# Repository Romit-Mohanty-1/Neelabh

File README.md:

## PCB for a 12-16v to 9V,25 watt buck(step down converter)

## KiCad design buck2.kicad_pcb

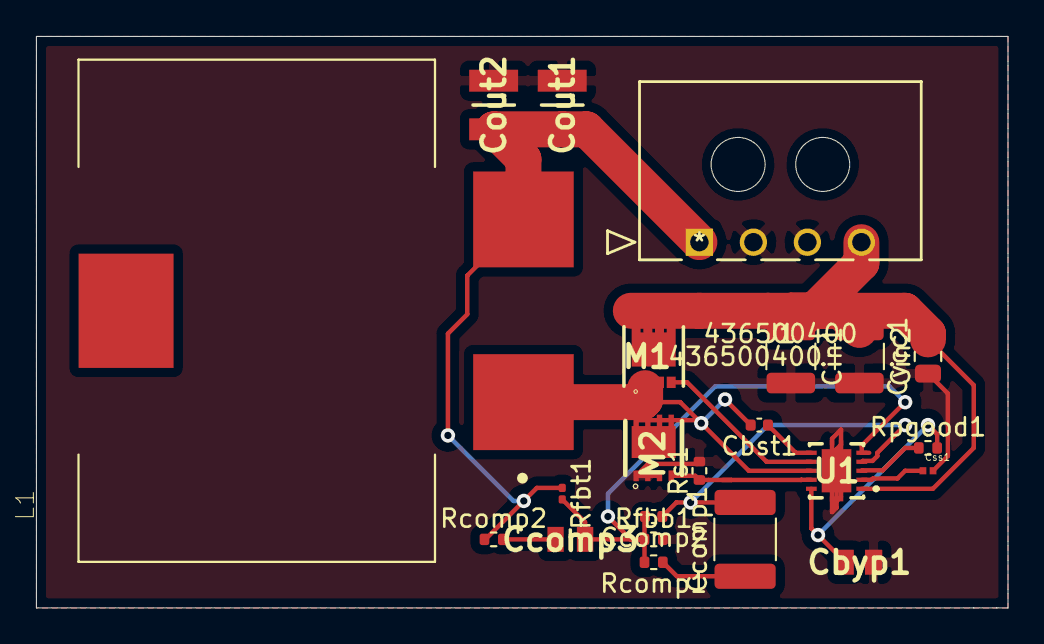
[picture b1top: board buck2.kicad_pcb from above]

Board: 2 copper layers, 54.0 x 31.8 mm, 22 parts (0 on the bottom side), 14 nets.

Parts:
Cbst1: 100nF,1mOhm; C_0402_1005Metric
Cbyp1: 2.2uF,1mOhm; CAPC2012X135N
Ccomp1: 18nF,0Ohm; C_1812_4532Metric
Ccomp2: 330pF,1mOhm; C_0402_1005Metric
Ccomp3: 4.7nF,0Ohm; CAPC2012X75N
Cin1, Cin2: 10uF,1mOhm; C_1210_3225Metric
Cout1, Cout2: 22uF,1mOhm; CAPC3225X270N
Css1: 3.3nF,1mOhm; CAPC0603X33N
Cvcc1: 1uF,1mOhm; C_0805_2012Metric
J1: 436500400
L1: SER2915L-223KL; IND_SER2915L-223KL
M1: 30V,56Amps; DQG_VSON-CLIP
M2: 30V,35Amps; Q3A
Rcomp1: 2.43kOhm; R_0402_1005Metric
Rcomp2: 191Ohm; R_0402_1005Metric
Rfbb1: 715Ohm; R_0402_1005Metric
Rfbt1: 10kOhm; R_0201_0603Metric
Rpgood1: 100kOhm; R_0402_1005Metric
Rs1: 1.87kOhm; R_0402_1005Metric
U1: TPS40303DRCR

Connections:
FB-1: Ccomp2.2, Ccomp3.2, Rcomp1.2, Rfbb1.1, Rfbt1.2, U1.5
unnamed: Cbst1.1, U1.6
unnamed: Cbst1.2, L1.1, M1.1, M1.2, M1.3, M2.5, M2.6, M2.7, M2.8, U1.8
unnamed: Cbyp1.1, Rpgood1.2, U1.10
unnamed: Ccomp1.1, Rcomp1.1
unnamed: Ccomp1.2, Ccomp2.1, U1.4
unnamed: Ccomp3.1, Rcomp2.2
unnamed: Css1.1, U1.2
unnamed: M1.4, U1.7
unnamed: M2.4, Rs1.1, U1.9
unnamed: Rpgood1.1, U1.3
Vin1: Cin1.1, Cin2.1, Cvcc1.2, J1.4, M1.5, M1.6, M1.7, M1.8, U1.1
Vin2: Cbyp1.2, Cin1.2, Cin2.2, Cout1.1, Cout2.1, Css1.2, Cvcc1.1, J1.2, J1.3, M2.1, M2.2, M2.3, Rfbb1.2, Rs1.2, U1.11, U1.12, U1.13, U1.14, U1.15
Vout1: Cout1.2, Cout2.2, J1.1, L1.2, Rcomp2.1, Rfbt1.1

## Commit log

2021-06-02 New cCommit
2021-06-03 more
2021-06-03 More new
